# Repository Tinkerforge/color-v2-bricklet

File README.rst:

Color Bricklet 2.0
==================

This repository contains the firmware source code and the hardware design
files. The documentation generator configs can be found at
https://github.com/Tinkerforge/generators

Repository Content
------------------

software/:
 * examples/: Examples for all supported languages
 * build/: Compiled files
 * src/: Source code of firmware
 * Makefile: Makefile to build project

hardware/:
 * Contains KiCad project files and additionally schematics as PDF

datasheets/:
 * Contains datasheets for sensors and complex ICs that are used

Hardware
--------

The hardware is designed with the open source EDA Suite KiCad
(http://www.kicad.org). Before you are able to open the files,
you have to install the Tinkerforge kicad-libraries
(https://github.com/Tinkerforge/kicad-libraries). You can either clone
them directly in hardware/ or clone them in a separate folder and
symlink them into hardware/
(ln -s kicad_path/kicad-libraries project_path/hardware). After that you
can open the .pro file in hardware/ with KiCad and from there view and
modify the schematics and the PCB layout.

Software
--------

If you want to do your own Brick/Bricklet firmware development we highly
recommend that you use our build environment setup script and read the
tutorial (https://www.tinkerforge.com/en/doc/Tutorials/Tutorial_Build_Environment/Tutorial.html).

To compile the C code we recommend you to install the newest GNU Arm Embedded
Toolchain (https://launchpad.net/gcc-arm-embedded/+download).
You also need to install bricklib2 (https://github.com/Tinkerforge/bricklib2).

You can either clone it directly in software/src/ or clone it in a
separate folder and symlink it into software/src/
(ln -s bricklib_path/bricklib2 project_path/software/src/). Finally make sure to
have CMake installed (http://www.cmake.org/cmake/resources/software.html).

After that you can build the firmware by invoking make in software/.
The firmware (.zbin) can then be found in software/build/ and uploaded
with brickv (click button "Flashing" on start screen).

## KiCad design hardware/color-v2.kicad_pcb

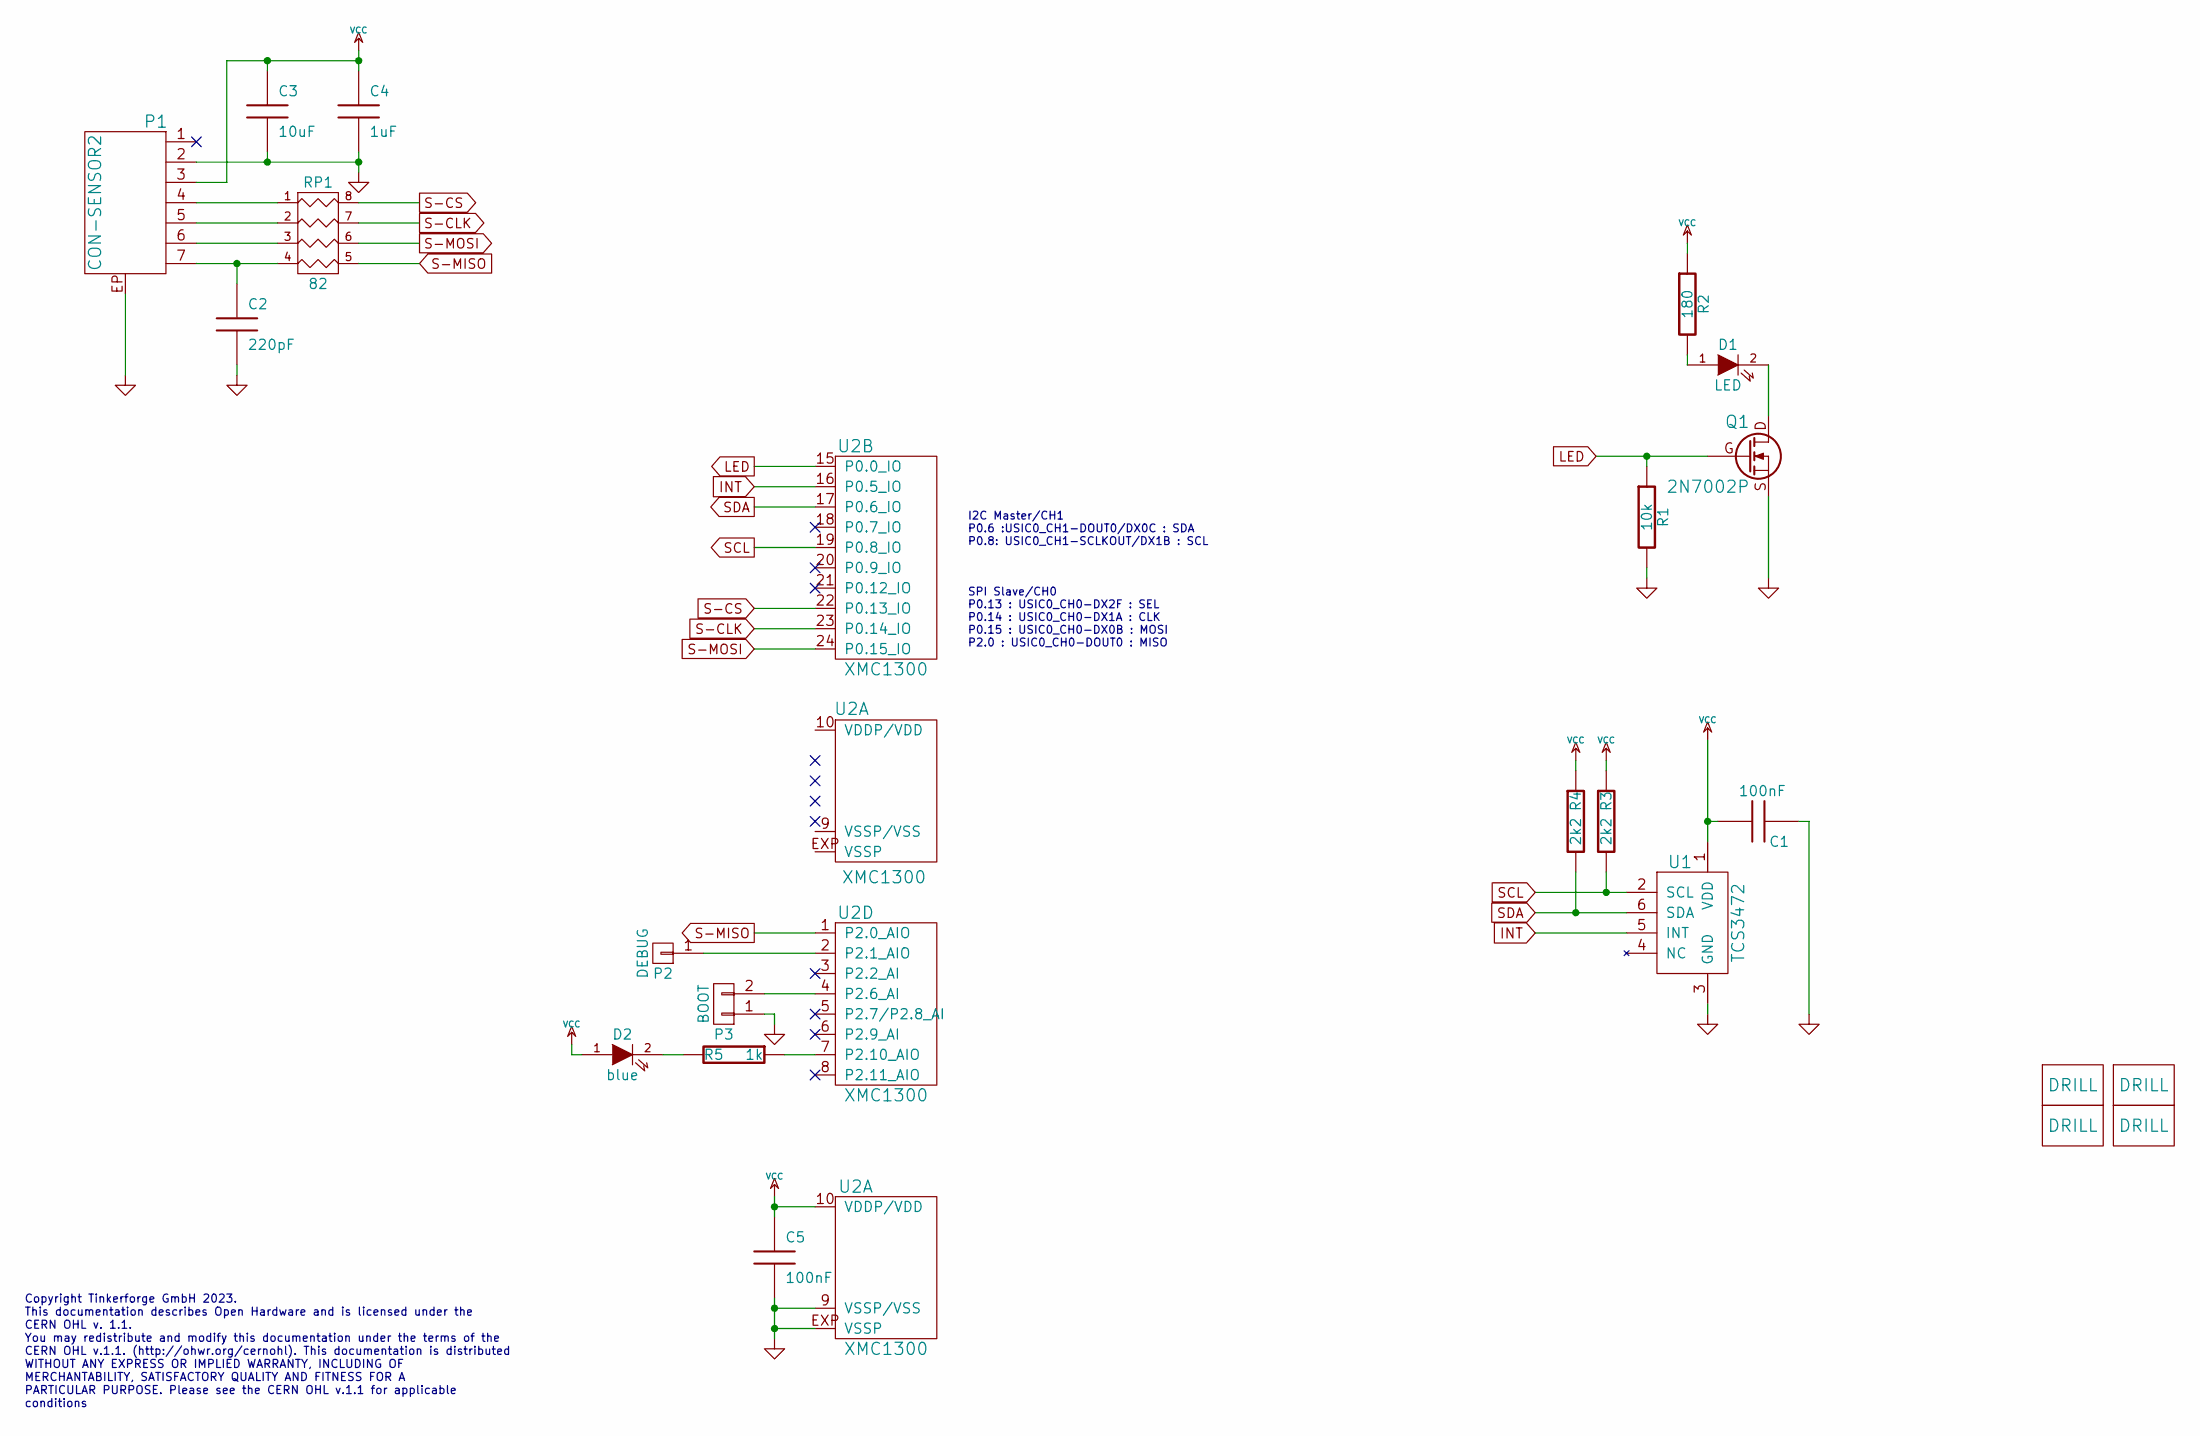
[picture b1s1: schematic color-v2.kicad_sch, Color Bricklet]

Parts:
C1, C5: 100nF; C0603F
C2: 220pF; C0402F
C3: 10uF; C0805
C4: 1uF; C0603F
D1: LED; LED-3x2
D2: blue; D0603F
P1: CON-SENSOR2
P2: DEBUG; DEBUG_PAD
P3: BOOT; SolderJumper
Q1: 2N7002P; SOT23GDS
R1: 10k; R0603F
R2: 180; R0603F
R3, R4: 2k2; R0603F
R5: 1k; R0603F
RP1: 82; 4X0402
U1: TCS3472; FN-TCS3472
U2: XMC1300; QFN24-4x4mm-0.5mm
U3, U4, U5, U6: DRILL; DRILL_NP

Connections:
GND: C1.1, C2.2, C3.2, C4.2, C5.2, P1.2, P1.EP, P3.1, Q1.S, R1.2, U1.3 (GND), U2.9 (VSSP/VSS), U2.EXP (VSSP)
INT: U1.5 (INT), U2.16 (P0.5_IO)
LED: Q1.G, R1.1, U2.15 (P0.0_IO)
unnamed: C2.1, P1.7, RP1.4
unnamed: D1.1 (A), R2.2
unnamed: D1.2 (K), Q1.D
unnamed: D2.2 (K), R5.2
unnamed: P1.4, RP1.1
unnamed: P1.5, RP1.2
unnamed: P1.6, RP1.3
unnamed: P2.1, U2.2 (P2.1_AIO)
unnamed: P3.2, U2.4 (P2.6_AI)
unnamed: R5.1, U2.7 (P2.10_AIO)
S-CLK: RP1.7 (R2), U2.23 (P0.14_IO)
S-CS: RP1.8 (R1), U2.22 (P0.13_IO)
S-MISO: RP1.5 (R4), U2.1 (P2.0_AIO)
S-MOSI: RP1.6 (R3), U2.24 (P0.15_IO)
SCL: R3.2, U1.2 (SCL), U2.19 (P0.8_IO)
SDA: R4.2, U1.6 (SDA), U2.17 (P0.6_IO)
VCC: C1.2, C3.1, C4.1, C5.1, D2.1 (A), P1.3, R2.1, R3.1, R4.1, U1.1 (VDD), U2.10 (VDDP/VDD)

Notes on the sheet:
I2C Master/CH1 P0.6 :USIC0_CH1-DOUT0/DX0C : SDA P0.8: USIC0_CH1-SCLKOUT/DX1B : SCL
Copyright Tinkerforge GmbH 2023. This documentation describes Open Hardware and is licensed under the CERN OHL v. 1.1. You may redistribute and modify this documentation under the terms of the CERN OHL v.1.1. (http://ohwr.org/cernohl). This documentation is distributed WITHOUT ANY EXPRESS OR IMPLIE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
SPI Slave/CH0 P0.13 : USIC0_CH0-DX2F : SEL P0.14 : USIC0_CH0-DX1A : CLK P0.15 : USIC0_CH0-DX0B : MOSI P2.0 : USIC0_CH0-DOUT0 : MISO

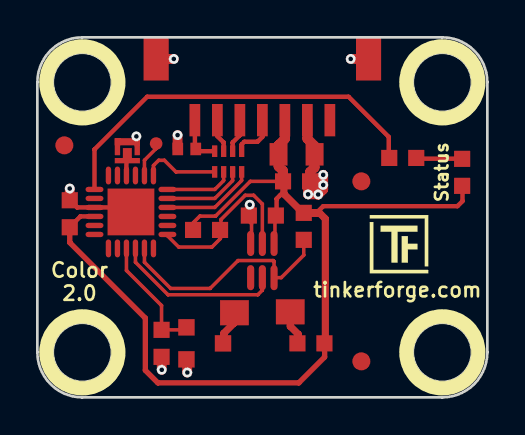
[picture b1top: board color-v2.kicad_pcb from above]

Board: 2 copper layers, 25.0 x 20.0 mm, 28 parts (2 on the bottom side), 20 nets.

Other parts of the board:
Fiducial_Mark: VAL**; Fiducial_Mark
Fiducial_Mark#2, Fiducial_Mark#3: VAL**; Fiducial_Mark
VAL: CE_5mm
VAL#2: WEEE_7mm

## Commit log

2018-06-27 Add datasheet
2018-06-27 Add schematic
2018-06-27 Add layout
2018-06-27 Fix layout
2018-07-11 Fix origin
2018-07-13 Add .gitignore
2018-07-27 Add auto-generated stub firmware
2019-01-17 fix drc error
2019-02-21 fixed library, added sym lib table
2019-02-21 changed colorsensor to TCS3472
2019-02-21 added fidutials
2019-04-08 changed to XMC1300
2019-04-08 Exchange VEML6040 for TCS34725 datasheet
2019-04-08 Add TCS3472 driver and Color V2 API
2019-05-03 Add auto-generated examples
2019-05-07 Apply bootloader pointer end fix to all new Bricklets
2019-05-14 Update rust examples.
2019-08-14 Turn logging off
2019-08-14 Add changelog entry for inital version
2019-08-15 add 3d data
2019-08-15 Rename set/get_config to set/get_configuration.
2019-08-22 c: Adapt to bindings changes
2019-08-22 Remove development marker
2020-01-13 examples: Use python3 input instead of python2 raw_input.
2020-01-13 examples: mqtt: Remove trailing whitespace.
2020-08-19 Add uc examples.
2020-08-25 uc: Fix whitespace
2020-08-27 uc: Fix warnings.
2020-08-31 uc: Use fixed-with placeholders in format strings.
2020-09-02 uc: Add example driver note.
2021-10-25 Update KiCad link
    https://www.kicad.org/blog/2021/10/Avoid-links-to-former-kicad-domain/
2022-04-19 examples: uc: Rename TF_HalContext to TF_HAL.
2022-04-27 uc: Adapt to bindings changes
2022-05-10 go: Fix format string
2022-07-06 Add license files.
2023-01-27 fix schematic
2023-01-27 add missing pro file
2023-01-27 remove old pro file
2023-01-27 Data Cleanup
2025-10-04 Fix compatibility with new Docker build image (GCC 14.2.1)

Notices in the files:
hardware/color-v2.kicad_pcb:
Licensed under CERN OHL v.1.1
Copyright (©) 2023, T.Schneidermann
